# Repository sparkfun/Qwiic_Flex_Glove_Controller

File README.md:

SparkFun Qwiic Flex Glove Controller
========================================

[*SparkFun Qwiic Flex Glove Controller (Sen-14666)*](https://www.sparkfun.com/products/14666)

This board is a breakout for multiple flex sensors that keeps the solder points isolated to avoid breakage in wearable projects.

Repository Contents
-------------------

* **/Hardware** - Eagle design files (.brd, .sch)
* **/Libraries** - Libraries for use with the <PRODUCT NAME>
* **/Production** - Production panel files (.brd)

Documentation
--------------
* **[ADS1015 Library](https://github.com/sparkfun/SparkFun_ADS1015_Arduino_Library)** - C++ library for the ADS1015.
* **[Hookup Guide](https://learn.sparkfun.com/tutorials/qwiic-flex-glove-controller-hookup-guide)** - Basic hookup guide for the Qwiic Flex Glove Controller.

Product Versions
----------------
* [SEN-14666](https://www.sparkfun.com/products/14666)- The SparkFun Qwiic Flex Glove Controller allows you to incorporate flex sensors into a glove to control lighting, sound, and other effects making it perfect for wearable and e-textile applications. All communication is enacted exclusively via I2C, utilizing our handy Qwiic system. 

License Information
-------------------

This product is _**open source**_! 

Please review the LICENSE.md file for license information. 

If you have any questions or concerns on licensing, please contact techsupport@sparkfun.com.

Distributed as-is; no warranty is given.

- Your friends at SparkFun.

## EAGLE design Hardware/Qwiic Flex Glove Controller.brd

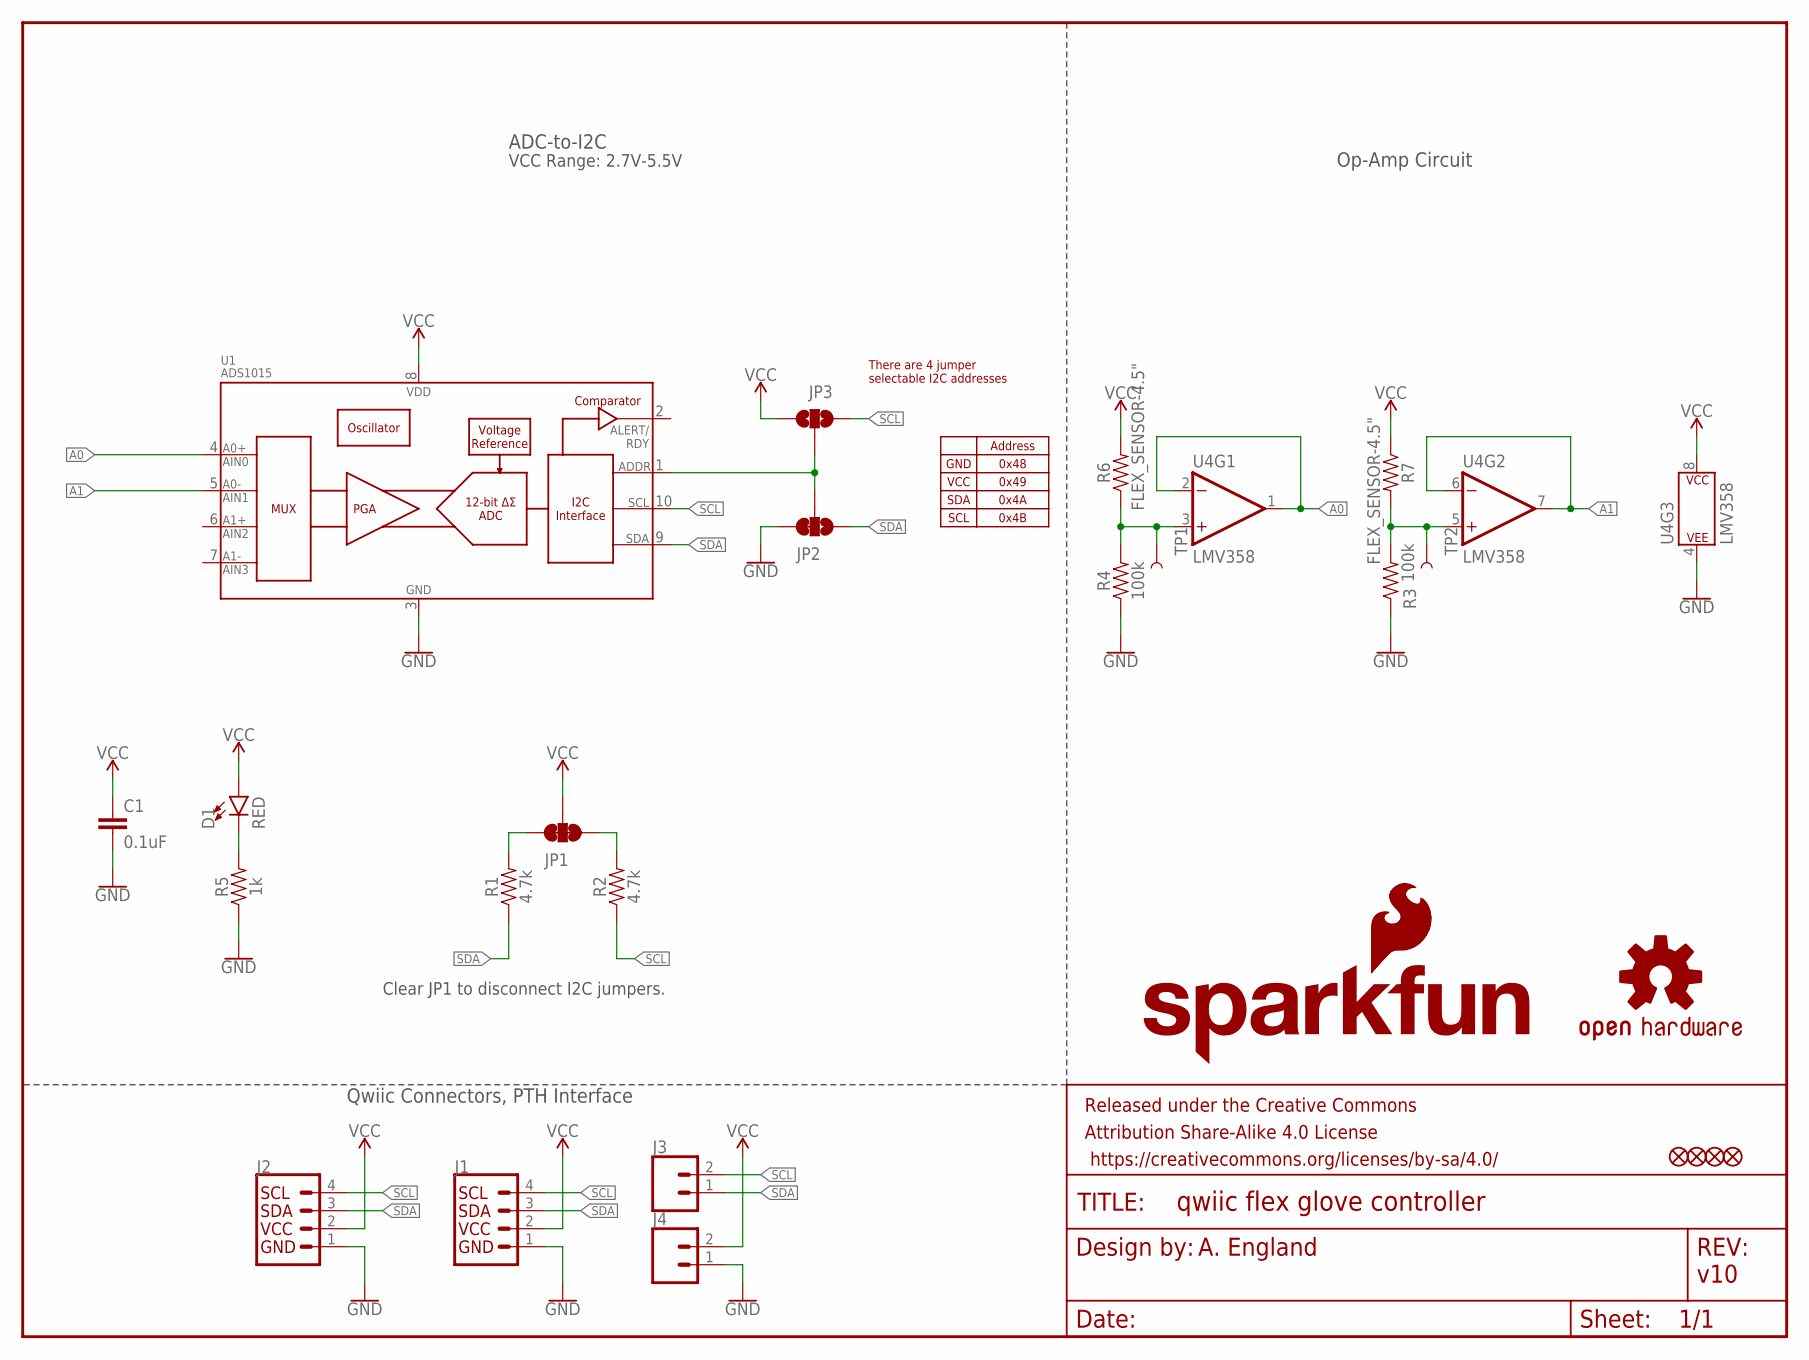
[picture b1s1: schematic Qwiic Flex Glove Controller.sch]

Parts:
C1: 0.1uF; 0603
D1: RED; LED-0603
FD1, FD2, FD3, FD4: FIDUCIALUFIDUCIAL; FIDUCIAL-MICRO
FRAME1: FRAME-LETTER; CREATIVE_COMMONS
J1, J2: QWIIC_CONNECTORJS-1MM; 1X04_1MM_RA
J3, J4: CONN_02; 1X02
JP1: JUMPER-SMT_3_2-NC_TRACE_NO-SILK; SMT-JUMPER_3_2-NC_TRACE_NO-SILK
JP2: JUMPER-SMT_3_1-NC_TRACE_NO-SILK; SMT-JUMPER_3_1-NC_TRACE_NO-SILK
JP3: JUMPER-SMT_3_NO_NO_SILK; SMT-JUMPER_3_0-NO_TRACE_NO-SILK
LOGO1: SFE_LOGO_NAME_FLAME.1_INCH; SFE_LOGO_NAME_FLAME_.1
LOGO2: OSHW-LOGOS; OSHW-LOGO-S
LOGO3: SFE_LOGO_FLAME.1_INCH; SFE_LOGO_FLAME_.1
R1, R2: 4.7k; 0603
R3, R4: 100k; 0603
R5: 1k; 0603
R6, R7: FLEX_SENSOR-4.5"; FLEX_SENSOR
TP1, TP2: TEST-POINT3; PAD.03X.03
U1: ADS1015; MSOP10
U4: LMV358; SO08

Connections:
A0: U1.4 (AIN0), U4.1 (OUT), U4.2 (-IN)
A1: U1.5 (AIN1), U4.6 (-IN), U4.7 (OUT)
GND: C1.2, J1.1, J2.1, J4.1, JP2.3, R3.1, R4.1, R5.1, U1.3 (VSS), U4.4 (P$V-)
unnamed: JP2.2, JP3.2, U1.1 (ADDR)
unnamed: D1.C, R5.2
unnamed: R3.2, R7.P$2 (2), TP2.P$1, U4.5 (+IN)
unnamed: R4.2, R6.P$1 (1), TP1.P$1, U4.3 (+IN)
unnamed: JP1.1, R2.2
unnamed: JP1.3, R1.2
SCL: J1.4, J2.4, J3.2, JP3.3, R2.1, U1.10 (SCL)
SDA: J1.3, J2.3, J3.1, JP2.1, R1.1, U1.9 (SDA)
VCC: C1.1, D1.A, J1.2, J2.2, J4.2, JP1.2, JP3.1, R6.P$2 (2), R7.P$1 (1), U1.8 (VDD), U4.8 (P$V+)

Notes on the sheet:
v10
Qwiic Connectors, PTH Interface
ADC-to-I2C
Op-Amp Circuit
A. England
There are 4 jumper selectable I2C addresses
Address
0x48
0x49
0x4A
0x4B
GND
VCC
SDA
SCL
VCC Range: 2.7V-5.5V
Clear JP1 to disconnect I2C jumpers.

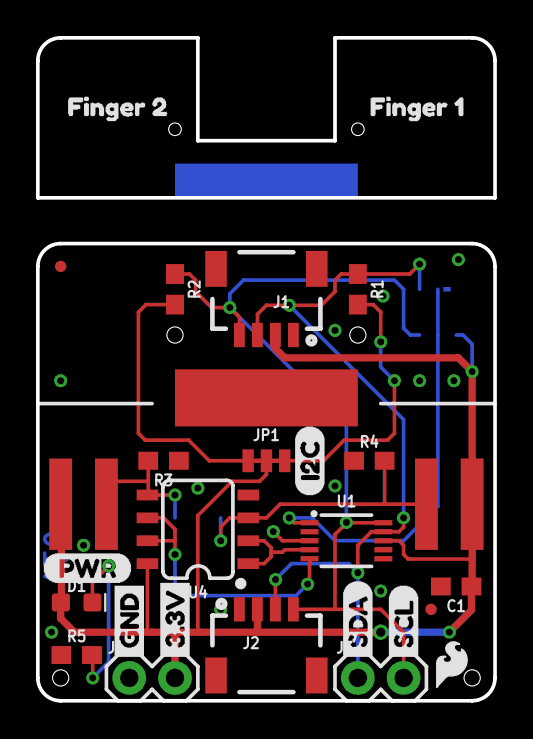
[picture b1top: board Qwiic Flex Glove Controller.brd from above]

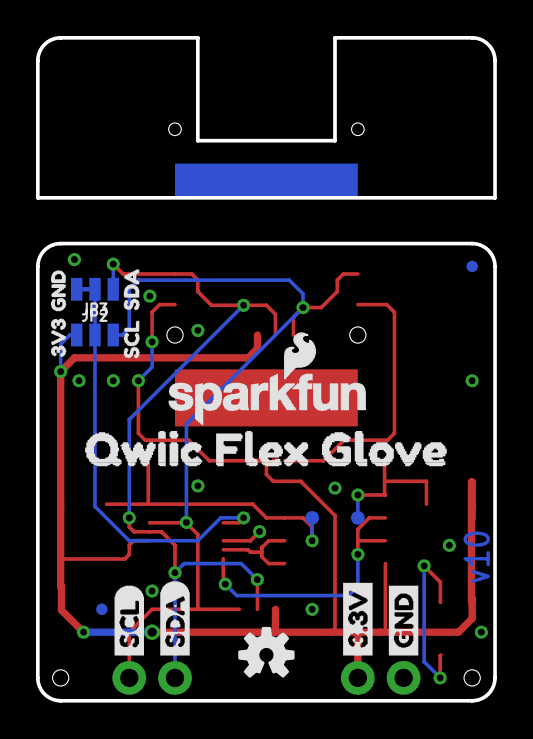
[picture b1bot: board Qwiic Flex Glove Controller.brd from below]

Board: 2 copper layers, 25.4 x 36.8 mm, 45 parts (17 on the bottom side), 12 nets.

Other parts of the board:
U$1, U$2: GND
U$3: 3V3-TEXT
U$4: GND-TEXT-03
U$5, U$6: 3.3V
U$7, U$8: SDA
U$9, U$10: SCL
U$11: (PWR)
U$12: SDA0
U$13: SCL2
U$14: QWIIC_FLEX_GLOVE0
U$15: I2C-()
U$16: FINGER_10
U$17: FINGER_21

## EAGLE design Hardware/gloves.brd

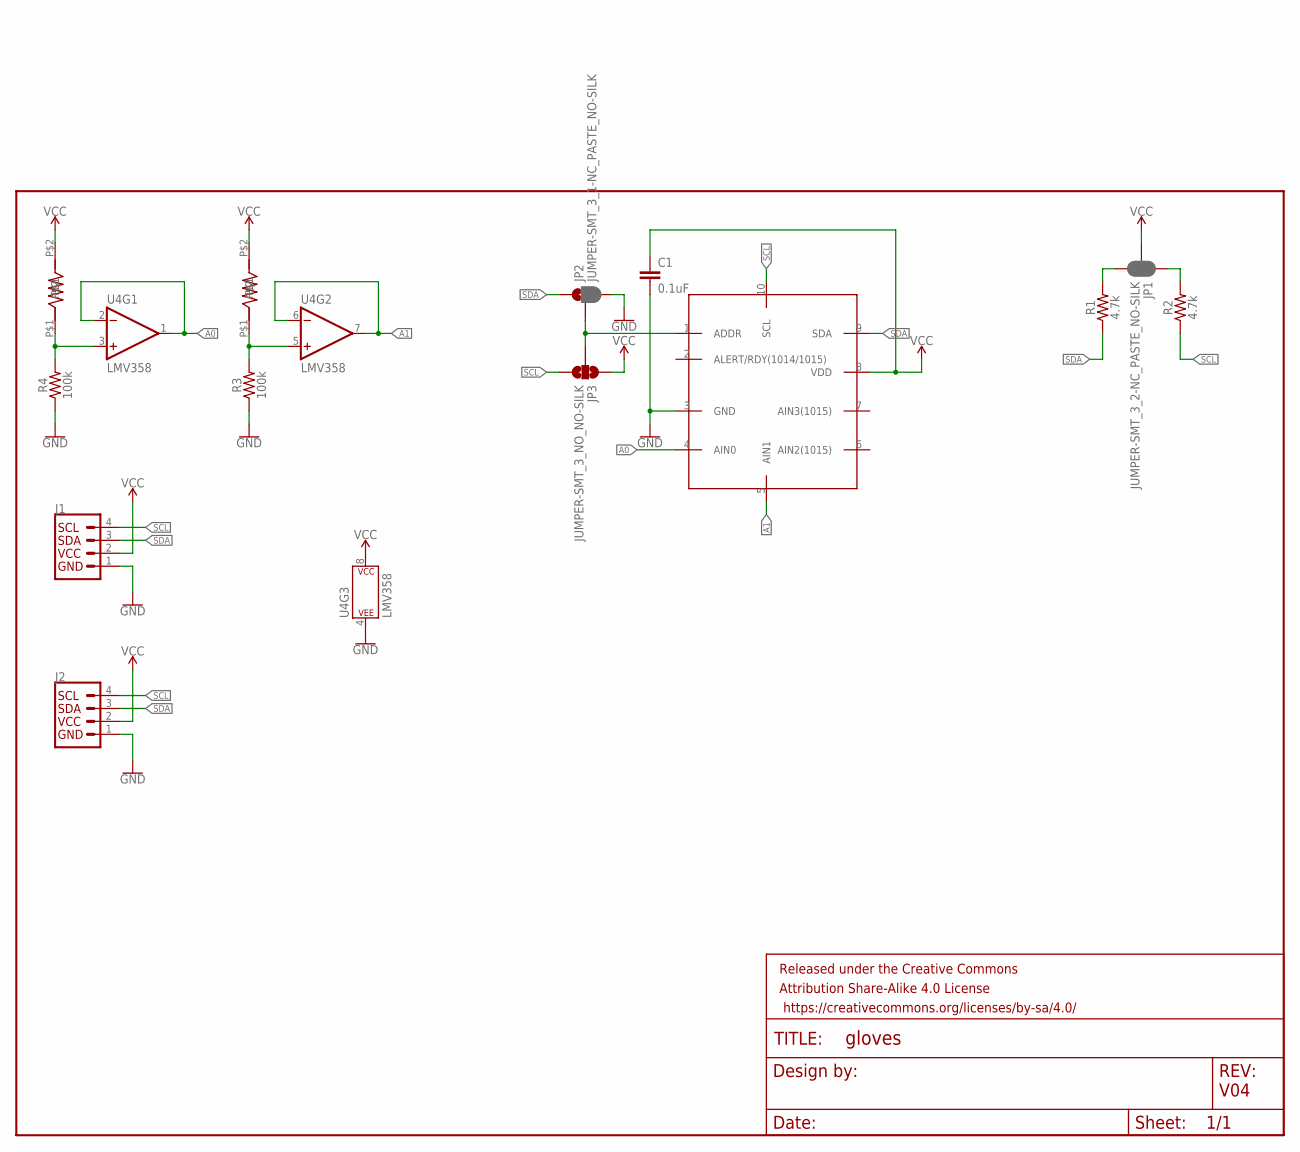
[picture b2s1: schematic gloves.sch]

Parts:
C1: 0.1uF; 0603
FRAME1: FRAME-LETTER; CREATIVE_COMMONS
J1, J2: QWIIC_CONNECTORJS-1MM; 1X04_1MM_RA
JP1: JUMPER-SMT_3_2-NC_PASTE_NO-SILK; SMT-JUMPER_3_2-NC_PASTE_NO-SILK
JP2: JUMPER-SMT_3_1-NC_PASTE_NO-SILK; SMT-JUMPER_3_1-NC_PASTE_NO-SILK
JP3: JUMPER-SMT_3_NO_NO-SILK; SMT-JUMPER_3_NO_NO-SILK
R1, R2: 4.7k; 0603
R3, R4: 100k; 0603
U4: LMV358; SO08
U$1: ADS101X-ADC_TO_I2CADS101X; MSOP-10-GNDPAD
U$3, U$4: FLEX_SENSOR

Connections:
A0: U4.1 (OUT), U4.2 (-IN), U$1.4 (AIN0)
A1: U4.6 (-IN), U4.7 (OUT), U$1.5 (AIN1)
GND: C1.2, J1.1, J2.1, JP2.3, R3.1, R4.1, U4.4 (P$V-), U$1.3 (GND)
unnamed: JP2.2, JP3.2, U$1.1 (ADDR)
unnamed: R3.2, U4.5 (+IN), U$3.P$1
unnamed: R4.2, U4.3 (+IN), U$4.P$1
unnamed: JP1.1, R2.2
unnamed: JP1.3, R1.2
SCL: J1.4, J2.4, JP3.3, R2.1, U$1.10 (SCL)
SDA: J1.3, J2.3, JP2.1, R1.1, U$1.9 (SDA)
VCC: C1.1, J1.2, J2.2, JP1.2, JP3.1, U4.8 (P$V+), U$1.8 (VDD), U$3.P$2, U$4.P$2

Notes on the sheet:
V04

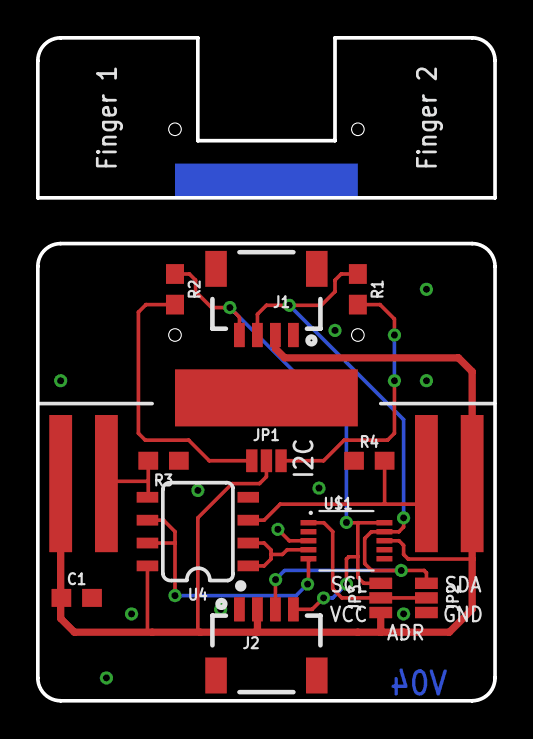
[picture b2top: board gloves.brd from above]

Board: 2 copper layers, 25.4 x 36.8 mm, 15 parts (0 on the bottom side), 11 nets.

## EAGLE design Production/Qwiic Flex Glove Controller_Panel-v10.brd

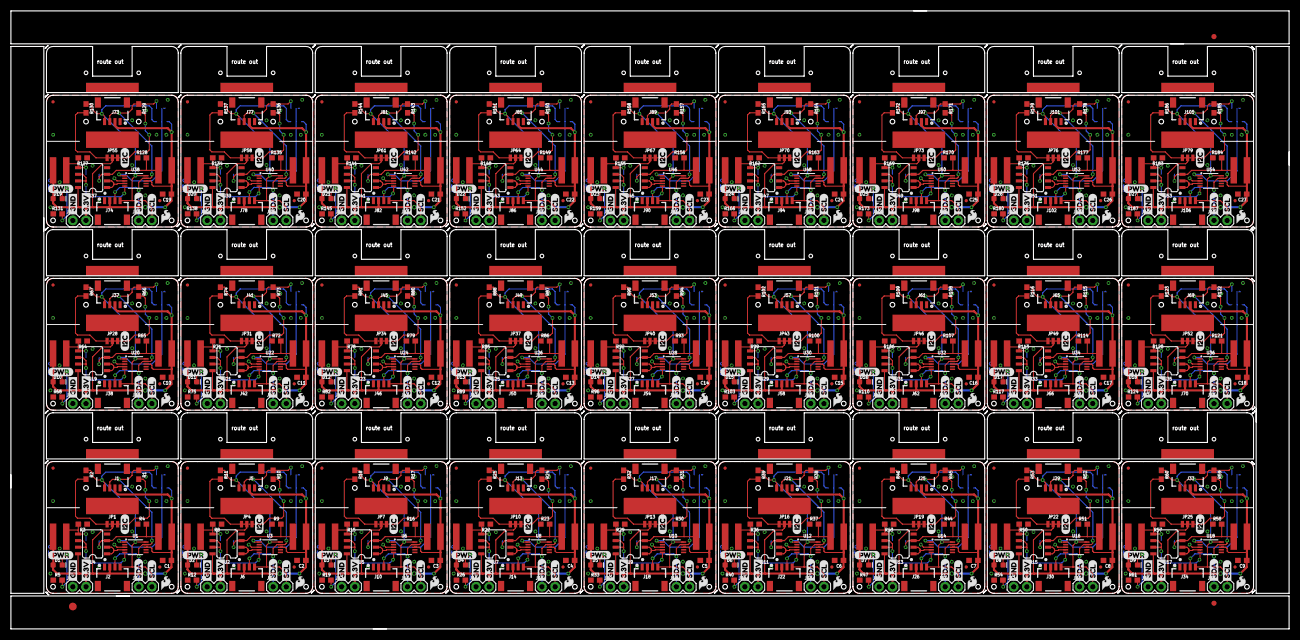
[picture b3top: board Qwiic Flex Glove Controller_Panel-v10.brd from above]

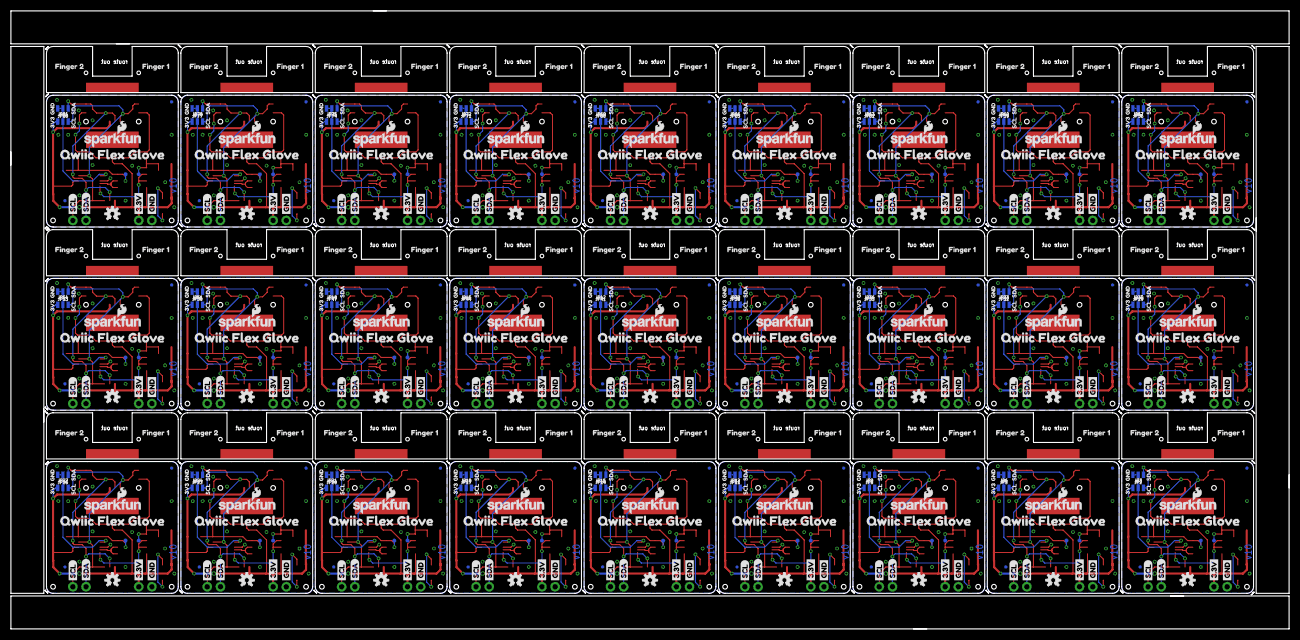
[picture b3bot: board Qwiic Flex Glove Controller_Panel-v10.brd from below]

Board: 2 copper layers, 246.4 x 119.1 mm, 1191 parts (513 on the bottom side), 324 nets.

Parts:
C1, C2, C3, C4, C5, C6, C7, C8, C9, C10, C11, C12, C13, C14, C15, C16, C17, C18, C19, C20, C21, C22, C23, C24, C25, C26, C27: 0.1uF; 0603
D1, D2, D3, D4, D5, D6, D7, D8, D9, D10, D11, D12, D13, D14, D15, D16, D17, D18, D19, D20, D21, D22, D23, D24, D25, D26, D27: RED; LED-0603
E$1: FIDUCIAL-1.5X3
E$5, E$6: FIDUCIAL-1X2
FD1, FD2, FD3, FD4, FD5, FD6, FD7, FD8, FD9, FD10, FD11, FD12, FD13, FD14, FD15, FD16, FD17, FD18, FD19, FD20, FD21, FD22, FD23, FD24, FD25, FD26, FD27, FD28, FD29, FD30, FD31, FD32, FD33, FD34, FD35, FD36, FD37, FD38, FD39, FD40, FD41, FD42, FD43, FD44, FD45, FD46, FD47, FD48, FD49, FD50, FD51, FD52, FD53, FD54, FD55, FD56, FD57, FD58, FD59, FD60, FD61, FD62, FD63, FD64, FD65, FD66, FD67, FD68, FD69, FD70, FD71, FD72, FD73, FD74, FD75, FD76, FD77, FD78, FD79, FD80, FD81, FD82, FD83, FD84, FD85, FD86, FD87, FD88, FD89, FD90, FD91, FD92, FD93, FD94, FD95, FD96, FD97, FD98, FD99, FD100, FD101, FD102, FD103, FD104, FD105, FD106, FD107, FD108: FIDUCIALUFIDUCIAL; FIDUCIAL-MICRO
J1, J2, J5, J6, J9, J10, J13, J14, J17, J18, J21, J22, J25, J26, J29, J30, J33, J34, J37, J38, J41, J42, J45, J46, J49, J50, J53, J54, J57, J58, J61, J62, J65, J66, J69, J70, J73, J74, J77, J78, J81, J82, J85, J86, J89, J90, J93, J94, J97, J98, J101, J102, J105, J106: 1X04_1MM_RA
J3, J4, J7, J8, J11, J12, J15, J16, J19, J20, J23, J24, J27, J28, J31, J32, J35, J36, J39, J40, J43, J44, J47, J48, J51, J52, J55, J56, J59, J60, J63, J64, J67, J68, J71, J72, J75, J76, J79, J80, J83, J84, J87, J88, J91, J92, J95, J96, J99, J100, J103, J104, J107, J108: 1X02
JP1, JP4, JP7, JP10, JP13, JP16, JP19, JP22, JP25, JP28, JP31, JP34, JP37, JP40, JP43, JP46, JP49, JP52, JP55, JP58, JP61, JP64, JP67, JP70, JP73, JP76, JP79: JUMPER-SMT_3_2-NC_TRACE_NO-SILK; SMT-JUMPER_3_2-NC_TRACE_NO-SILK
JP2, JP5, JP8, JP11, JP14, JP17, JP20, JP23, JP26, JP29, JP32, JP35, JP38, JP41, JP44, JP47, JP50, JP53, JP56, JP59, JP62, JP65, JP68, JP71, JP74, JP77, JP80: JUMPER-SMT_3_1-NC_TRACE_NO-SILK; SMT-JUMPER_3_1-NC_TRACE_NO-SILK
JP3, JP6, JP9, JP12, JP15, JP18, JP21, JP24, JP27, JP30, JP33, JP36, JP39, JP42, JP45, JP48, JP51, JP54, JP57, JP60, JP63, JP66, JP69, JP72, JP75, JP78, JP81: JUMPER-SMT_3_NO_NO_SILK; SMT-JUMPER_3_0-NO_TRACE_NO-SILK
LOGO1, LOGO4, LOGO7, LOGO10, LOGO13, LOGO16, LOGO19, LOGO22, LOGO25, LOGO28, LOGO31, LOGO34, LOGO37, LOGO40, LOGO43, LOGO46, LOGO49, LOGO52, LOGO55, LOGO58, LOGO61, LOGO64, LOGO67, LOGO70, LOGO73, LOGO76, LOGO79: SFE_LOGO_NAME_FLAME.1_INCH; SFE_LOGO_NAME_FLAME_.1
LOGO2, LOGO5, LOGO8, LOGO11, LOGO14, LOGO17, LOGO20, LOGO23, LOGO26, LOGO29, LOGO32, LOGO35, LOGO38, LOGO41, LOGO44, LOGO47, LOGO50, LOGO53, LOGO56, LOGO59, LOGO62, LOGO65, LOGO68, LOGO71, LOGO74, LOGO77, LOGO80: OSHW-LOGOS; OSHW-LOGO-S
LOGO3, LOGO6, LOGO9, LOGO12, LOGO15, LOGO18, LOGO21, LOGO24, LOGO27, LOGO30, LOGO33, LOGO36, LOGO39, LOGO42, LOGO45, LOGO48, LOGO51, LOGO54, LOGO57, LOGO60, LOGO63, LOGO66, LOGO69, LOGO72, LOGO75, LOGO78, LOGO81: SFE_LOGO_FLAME.1_INCH; SFE_LOGO_FLAME_.1
R1, R2, R10, R11, R17, R18, R24, R25, R31, R32, R38, R39, R45, R46, R52, R53, R59, R60, R66, R67, R73, R74, R80, R81, R87, R88, R94, R95, R101, R102, R108, R109, R115, R116, R122, R123, R129, R130, R136, R137, R143, R144, R150, R151, R157, R158, R164, R165, R171, R172, R178, R179, R185, R186: 4.7k; 0603
R3, R4, R8, R9, R15, R16, R22, R23, R29, R30, R36, R37, R43, R44, R50, R51, R57, R58, R64, R65, R71, R72, R78, R79, R85, R86, R92, R93, R99, R100, R106, R107, R113, R114, R120, R121, R127, R128, R134, R135, R141, R142, R148, R149, R155, R156, R162, R163, R169, R170, R176, R177, R183, R184: 100k; 0603
R5, R12, R19, R26, R33, R40, R47, R54, R61, R68, R75, R82, R89, R96, R103, R110, R117, R124, R131, R138, R145, R152, R159, R166, R173, R180, R187: 1k; 0603
R6, R7, R13, R14, R20, R21, R27, R28, R34, R35, R41, R42, R48, R49, R55, R56, R62, R63, R69, R70, R76, R77, R83, R84, R90, R91, R97, R98, R104, R105, R111, R112, R118, R119, R125, R126, R132, R133, R139, R140, R146, R147, R153, R154, R160, R161, R167, R168, R174, R175, R181, R182, R188, R189: FLEX_SENSOR-4.5"; FLEX_SENSOR
TP1, TP2, TP3, TP4, TP5, TP6, TP7, TP8, TP9, TP10, TP11, TP12, TP13, TP14, TP15, TP16, TP17, TP18, TP19, TP20, TP21, TP22, TP23, TP24, TP25, TP26, TP27, TP28, TP29, TP30, TP31, TP32, TP33, TP34, TP35, TP36, TP37, TP38, TP39, TP40, TP41, TP42, TP43, TP44, TP45, TP46, TP47, TP48, TP49, TP50, TP51, TP52, TP53, TP54: TEST-POINT3; PAD.03X.03
U1, U3, U6, U8, U10, U12, U14, U16, U18, U20, U22, U24, U26, U28, U30, U32, U34, U36, U38, U40, U42, U44, U46, U48, U50, U52, U54: ADS1015; MSOP10
U2, U4, U5, U7, U9, U11, U13, U15, U17, U19, U21, U23, U25, U27, U29, U31, U33, U35, U37, U39, U41, U43, U45, U47, U49, U51, U53: LMV358; SO08
U$1, U$2, U$18, U$19, U$35, U$36, U$52, U$53, U$69, U$70, U$86, U$87, U$103, U$104, U$120, U$121, U$137, U$138, U$154, U$155, U$171, U$172, U$188, U$189, U$205, U$206, U$222, U$223, U$239, U$240, U$256, U$257, U$273, U$274, U$290, U$291, U$307, U$308, U$324, U$325, U$341, U$342, U$358, U$359, U$375, U$376, U$392, U$393, U$409, U$410, U$426, U$427, U$443, U$444: GND
U$3, U$27, U$44, U$61, U$78, U$95, U$112, U$129, U$146, U$163, U$180, U$197, U$214, U$231, U$248, U$265, U$282, U$299, U$316, U$333, U$350, U$367, U$384, U$401, U$418, U$435, U$452: 3V3-TEXT
U$4, U$28, U$45, U$62, U$79, U$96, U$113, U$130, U$147, U$164, U$181, U$198, U$215, U$232, U$249, U$266, U$283, U$300, U$317, U$334, U$351, U$368, U$385, U$402, U$419, U$436, U$453: GND-TEXT-03
U$5, U$6, U$20, U$21, U$37, U$38, U$54, U$55, U$71, U$72, U$88, U$89, U$105, U$106, U$122, U$123, U$139, U$140, U$156, U$157, U$173, U$174, U$190, U$191, U$207, U$208, U$224, U$225, U$241, U$242, U$258, U$259, U$275, U$276, U$292, U$293, U$309, U$310, U$326, U$327, U$343, U$344, U$360, U$361, U$377, U$378, U$394, U$395, U$411, U$412, U$428, U$429, U$445, U$446: 3.3V
U$7, U$8, U$22, U$23, U$39, U$40, U$56, U$57, U$73, U$74, U$90, U$91, U$107, U$108, U$124, U$125, U$141, U$142, U$158, U$159, U$175, U$176, U$192, U$193, U$209, U$210, U$226, U$227, U$243, U$244, U$260, U$261, U$277, U$278, U$294, U$295, U$311, U$312, U$328, U$329, U$345, U$346, U$362, U$363, U$379, U$380, U$396, U$397, U$413, U$414, U$430, U$431, U$447, U$448: SDA
U$9, U$10, U$24, U$25, U$41, U$42, U$58, U$59, U$75, U$76, U$92, U$93, U$109, U$110, U$126, U$127, U$143, U$144, U$160, U$161, U$177, U$178, U$194, U$195, U$211, U$212, U$228, U$229, U$245, U$246, U$262, U$263, U$279, U$280, U$296, U$297, U$313, U$314, U$330, U$331, U$347, U$348, U$364, U$365, U$381, U$382, U$398, U$399, U$415, U$416, U$432, U$433, U$449, U$450: SCL
U$11, U$26, U$43, U$60, U$77, U$94, U$111, U$128, U$145, U$162, U$179, U$196, U$213, U$230, U$247, U$264, U$281, U$298, U$315, U$332, U$349, U$366, U$383, U$400, U$417, U$434, U$451: (PWR)
U$12, U$29, U$46, U$63, U$80, U$97, U$114, U$131, U$148, U$165, U$182, U$199, U$216, U$233, U$250, U$267, U$284, U$301, U$318, U$335, U$352, U$369, U$386, U$403, U$420, U$437, U$454: SDA0
U$13, U$30, U$47, U$64, U$81, U$98, U$115, U$132, U$149, U$166, U$183, U$200, U$217, U$234, U$251, U$268, U$285, U$302, U$319, U$336, U$353, U$370, U$387, U$404, U$421, U$438, U$455: SCL2
U$14, U$32, U$49, U$66, U$83, U$100, U$117, U$134, U$151, U$168, U$185, U$202, U$219, U$236, U$253, U$270, U$287, U$304, U$321, U$338, U$355, U$372, U$389, U$406, U$423, U$440, U$457: QWIIC_FLEX_GLOVE0
U$15, U$31, U$48, U$65, U$82, U$99, U$116, U$133, U$150, U$167, U$184, U$201, U$218, U$235, U$252, U$269, U$286, U$303, U$320, U$337, U$354, U$371, U$388, U$405, U$422, U$439, U$456: I2C-()
U$16, U$33, U$50, U$67, U$84, U$101, U$118, U$135, U$152, U$169, U$186, U$203, U$220, U$237, U$254, U$271, U$288, U$305, U$322, U$339, U$356, U$373, U$390, U$407, U$424, U$441, U$458: FINGER_10
U$17, U$34, U$51, U$68, U$85, U$102, U$119, U$136, U$153, U$170, U$187, U$204, U$221, U$238, U$255, U$272, U$289, U$306, U$323, U$340, U$357, U$374, U$391, U$408, U$425, U$442, U$459: FINGER_21

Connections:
A0: U1.4, U4.1, U4.2
A1: U1.5, U4.6, U4.7
A2: U2.1, U2.2, U3.4
A3: U2.6, U2.7, U3.5
A4: U5.1, U5.2, U6.4
A5: U5.6, U5.7, U6.5
A6: U7.1, U7.2, U8.4
A7: U7.6, U7.7, U8.5
A8: U9.1, U9.2, U10.4
A9: U9.6, U9.7, U10.5
A10: U11.1, U11.2, U12.4
A11: U11.6, U11.7, U12.5
A12: U13.1, U13.2, U14.4
A13: U13.6, U13.7, U14.5
A14: U15.1, U15.2, U16.4
A15: U15.6, U15.7, U16.5
A16: U17.1, U17.2, U18.4
A17: U17.6, U17.7, U18.5
A18: U19.1, U19.2, U20.4
A19: U19.6, U19.7, U20.5
A20: U21.1, U21.2, U22.4
A21: U21.6, U21.7, U22.5
A22: U23.1, U23.2, U24.4
A23: U23.6, U23.7, U24.5
A24: U25.1, U25.2, U26.4
A25: U25.6, U25.7, U26.5
A26: U27.1, U27.2, U28.4
A27: U27.6, U27.7, U28.5
A28: U29.1, U29.2, U30.4
A29: U29.6, U29.7, U30.5
A30: U31.1, U31.2, U32.4
A31: U31.6, U31.7, U32.5
A32: U33.1, U33.2, U34.4
A33: U33.6, U33.7, U34.5
A34: U35.1, U35.2, U36.4
A35: U35.6, U35.7, U36.5
A36: U37.1, U37.2, U38.4
A37: U37.6, U37.7, U38.5
A38: U39.1, U39.2, U40.4
A39: U39.6, U39.7, U40.5
A40: U41.1, U41.2, U42.4
A41: U41.6, U41.7, U42.5
A42: U43.1, U43.2, U44.4
A43: U43.6, U43.7, U44.5
A44: U45.1, U45.2, U46.4
A45: U45.6, U45.7, U46.5
A46: U47.1, U47.2, U48.4
A47: U47.6, U47.7, U48.5
A48: U49.1, U49.2, U50.4
A49: U49.6, U49.7, U50.5
A50: U51.1, U51.2, U52.4
A51: U51.6, U51.7, U52.5
A52: U53.1, U53.2, U54.4
A53: U53.6, U53.7, U54.5
GND: C1.2, J1.1, J2.1, J4.1, JP2.3, R3.1, R4.1, R5.1, U1.3, U4.4
GND1: C2.2, J5.1, J6.1, J8.1, JP5.3, R8.1, R9.1, R12.1, U2.4, U3.3
GND2: C3.2, J9.1, J10.1, J12.1, JP8.3, R15.1, R16.1, R19.1, U5.4, U6.3
GND3: C4.2, J13.1, J14.1, J16.1, JP11.3, R22.1, R23.1, R26.1, U7.4, U8.3
GND4: C5.2, J17.1, J18.1, J20.1, JP14.3, R29.1, R30.1, R33.1, U9.4, U10.3
GND5: C6.2, J21.1, J22.1, J24.1, JP17.3, R36.1, R37.1, R40.1, U11.4, U12.3
GND6: C7.2, J25.1, J26.1, J28.1, JP20.3, R43.1, R44.1, R47.1, U13.4, U14.3
GND7: C8.2, J29.1, J30.1, J32.1, JP23.3, R50.1, R51.1, R54.1, U15.4, U16.3
GND8: C9.2, J33.1, J34.1, J36.1, JP26.3, R57.1, R58.1, R61.1, U17.4, U18.3
GND9: C10.2, J37.1, J38.1, J40.1, JP29.3, R64.1, R65.1, R68.1, U19.4, U20.3
GND10: C11.2, J41.1, J42.1, J44.1, JP32.3, R71.1, R72.1, R75.1, U21.4, U22.3
GND11: C12.2, J45.1, J46.1, J48.1, JP35.3, R78.1, R79.1, R82.1, U23.4, U24.3
GND12: C13.2, J49.1, J50.1, J52.1, JP38.3, R85.1, R86.1, R89.1, U25.4, U26.3
GND13: C14.2, J53.1, J54.1, J56.1, JP41.3, R92.1, R93.1, R96.1, U27.4, U28.3
GND14: C15.2, J57.1, J58.1, J60.1, JP44.3, R99.1, R100.1, R103.1, U29.4, U30.3
GND15: C16.2, J61.1, J62.1, J64.1, JP47.3, R106.1, R107.1, R110.1, U31.4, U32.3
GND16: C17.2, J65.1, J66.1, J68.1, JP50.3, R113.1, R114.1, R117.1, U33.4, U34.3
GND17: C18.2, J69.1, J70.1, J72.1, JP53.3, R120.1, R121.1, R124.1, U35.4, U36.3
GND18: C19.2, J73.1, J74.1, J76.1, JP56.3, R127.1, R128.1, R131.1, U37.4, U38.3
GND19: C20.2, J77.1, J78.1, J80.1, JP59.3, R134.1, R135.1, R138.1, U39.4, U40.3
GND20: C21.2, J81.1, J82.1, J84.1, JP62.3, R141.1, R142.1, R145.1, U41.4, U42.3
GND21: C22.2, J85.1, J86.1, J88.1, JP65.3, R148.1, R149.1, R152.1, U43.4, U44.3
GND22: C23.2, J89.1, J90.1, J92.1, JP68.3, R155.1, R156.1, R159.1, U45.4, U46.3
GND23: C24.2, J93.1, J94.1, J96.1, JP71.3, R162.1, R163.1, R166.1, U47.4, U48.3
GND24: C25.2, J97.1, J98.1, J100.1, JP74.3, R169.1, R170.1, R173.1, U49.4, U50.3
GND25: C26.2, J101.1, J102.1, J104.1, JP77.3, R176.1, R177.1, R180.1, U51.4, U52.3
GND26: C27.2, J105.1, J106.1, J108.1, JP80.3, R183.1, R184.1, R187.1, U53.4, U54.3
unnamed: JP2.2, JP3.2, U1.1
unnamed: D1.C, R5.2
unnamed: R3.2, R7.P$2, TP2.P$1, U4.5
unnamed: R4.2, R6.P$1, TP1.P$1, U4.3
unnamed: R8.2, R14.P$2, TP4.P$1, U2.5
unnamed: R9.2, R13.P$1, TP3.P$1, U2.3
unnamed: JP1.1, R2.2
unnamed: JP1.3, R1.2
unnamed: JP4.1, R11.2
unnamed: JP4.3, R10.2
unnamed: JP5.2, JP6.2, U3.1
unnamed: D2.C, R12.2
unnamed: R15.2, R21.P$2, TP6.P$1, U5.5
unnamed: R16.2, R20.P$1, TP5.P$1, U5.3
unnamed: JP7.1, R18.2
unnamed: JP7.3, R17.2
unnamed: JP8.2, JP9.2, U6.1
unnamed: D3.C, R19.2
unnamed: R22.2, R28.P$2, TP8.P$1, U7.5
unnamed: R23.2, R27.P$1, TP7.P$1, U7.3
unnamed: JP10.1, R25.2
unnamed: JP10.3, R24.2
unnamed: JP11.2, JP12.2, U8.1
unnamed: D4.C, R26.2
unnamed: R29.2, R35.P$2, TP10.P$1, U9.5
unnamed: R30.2, R34.P$1, TP9.P$1, U9.3
unnamed: JP13.1, R32.2
unnamed: JP13.3, R31.2
unnamed: JP14.2, JP15.2, U10.1
unnamed: D5.C, R33.2
unnamed: R36.2, R42.P$2, TP12.P$1, U11.5
unnamed: R37.2, R41.P$1, TP11.P$1, U11.3
unnamed: JP16.1, R39.2
unnamed: JP16.3, R38.2
unnamed: JP17.2, JP18.2, U12.1
unnamed: D6.C, R40.2
unnamed: R43.2, R49.P$2, TP14.P$1, U13.5
unnamed: R44.2, R48.P$1, TP13.P$1, U13.3
unnamed: JP19.1, R46.2
unnamed: JP19.3, R45.2
unnamed: JP20.2, JP21.2, U14.1
unnamed: D7.C, R47.2
unnamed: R50.2, R56.P$2, TP16.P$1, U15.5
unnamed: R51.2, R55.P$1, TP15.P$1, U15.3
unnamed: JP22.1, R53.2
unnamed: JP22.3, R52.2
unnamed: JP23.2, JP24.2, U16.1
unnamed: D8.C, R54.2
unnamed: R57.2, R63.P$2, TP18.P$1, U17.5
unnamed: R58.2, R62.P$1, TP17.P$1, U17.3
unnamed: JP25.1, R60.2
unnamed: JP25.3, R59.2
unnamed: JP26.2, JP27.2, U18.1
unnamed: D9.C, R61.2
unnamed: R64.2, R70.P$2, TP20.P$1, U19.5
unnamed: R65.2, R69.P$1, TP19.P$1, U19.3
unnamed: JP28.1, R67.2
unnamed: JP28.3, R66.2
unnamed: JP29.2, JP30.2, U20.1
unnamed: D10.C, R68.2
unnamed: R71.2, R77.P$2, TP22.P$1, U21.5
unnamed: R72.2, R76.P$1, TP21.P$1, U21.3
unnamed: JP31.1, R74.2
unnamed: JP31.3, R73.2
unnamed: JP32.2, JP33.2, U22.1
unnamed: D11.C, R75.2
unnamed: R78.2, R84.P$2, TP24.P$1, U23.5
unnamed: R79.2, R83.P$1, TP23.P$1, U23.3
unnamed: JP34.1, R81.2
unnamed: JP34.3, R80.2
unnamed: JP35.2, JP36.2, U24.1
unnamed: D12.C, R82.2
unnamed: R85.2, R91.P$2, TP26.P$1, U25.5
unnamed: R86.2, R90.P$1, TP25.P$1, U25.3
unnamed: JP37.1, R88.2
unnamed: JP37.3, R87.2
unnamed: JP38.2, JP39.2, U26.1
unnamed: D13.C, R89.2
unnamed: R92.2, R98.P$2, TP28.P$1, U27.5
unnamed: R93.2, R97.P$1, TP27.P$1, U27.3
unnamed: JP40.1, R95.2
unnamed: JP40.3, R94.2
unnamed: JP41.2, JP42.2, U28.1
unnamed: D14.C, R96.2
unnamed: R99.2, R105.P$2, TP30.P$1, U29.5
unnamed: R100.2, R104.P$1, TP29.P$1, U29.3
unnamed: JP43.1, R102.2
unnamed: JP43.3, R101.2
unnamed: JP44.2, JP45.2, U30.1
unnamed: D15.C, R103.2
unnamed: R106.2, R112.P$2, TP32.P$1, U31.5
unnamed: R107.2, R111.P$1, TP31.P$1, U31.3
unnamed: JP46.1, R109.2
unnamed: JP46.3, R108.2
unnamed: JP47.2, JP48.2, U32.1
unnamed: D16.C, R110.2
unnamed: R113.2, R119.P$2, TP34.P$1, U33.5
unnamed: R114.2, R118.P$1, TP33.P$1, U33.3
unnamed: JP49.1, R116.2
unnamed: JP49.3, R115.2
unnamed: JP50.2, JP51.2, U34.1
unnamed: D17.C, R117.2
unnamed: R120.2, R126.P$2, TP36.P$1, U35.5
unnamed: R121.2, R125.P$1, TP35.P$1, U35.3
unnamed: JP52.1, R123.2
unnamed: JP52.3, R122.2
unnamed: JP53.2, JP54.2, U36.1
unnamed: D18.C, R124.2
unnamed: R127.2, R133.P$2, TP38.P$1, U37.5
unnamed: R128.2, R132.P$1, TP37.P$1, U37.3
unnamed: JP55.1, R130.2
unnamed: JP55.3, R129.2
unnamed: JP56.2, JP57.2, U38.1
unnamed: D19.C, R131.2
unnamed: R134.2, R140.P$2, TP40.P$1, U39.5
unnamed: R135.2, R139.P$1, TP39.P$1, U39.3
unnamed: JP58.1, R137.2
unnamed: JP58.3, R136.2
unnamed: JP59.2, JP60.2, U40.1
unnamed: D20.C, R138.2
unnamed: R141.2, R147.P$2, TP42.P$1, U41.5
unnamed: R142.2, R146.P$1, TP41.P$1, U41.3
unnamed: JP61.1, R144.2
unnamed: JP61.3, R143.2
unnamed: JP62.2, JP63.2, U42.1
unnamed: D21.C, R145.2
unnamed: R148.2, R154.P$2, TP44.P$1, U43.5
unnamed: R149.2, R153.P$1, TP43.P$1, U43.3
unnamed: JP64.1, R151.2
unnamed: JP64.3, R150.2
unnamed: JP65.2, JP66.2, U44.1
unnamed: D22.C, R152.2
unnamed: R155.2, R161.P$2, TP46.P$1, U45.5
unnamed: R156.2, R160.P$1, TP45.P$1, U45.3
unnamed: JP67.1, R158.2
unnamed: JP67.3, R157.2
unnamed: JP68.2, JP69.2, U46.1
unnamed: D23.C, R159.2
unnamed: R162.2, R168.P$2, TP48.P$1, U47.5
unnamed: R163.2, R167.P$1, TP47.P$1, U47.3
unnamed: JP70.1, R165.2
unnamed: JP70.3, R164.2
unnamed: JP71.2, JP72.2, U48.1
unnamed: D24.C, R166.2
unnamed: R169.2, R175.P$2, TP50.P$1, U49.5
unnamed: R170.2, R174.P$1, TP49.P$1, U49.3
unnamed: JP73.1, R172.2
unnamed: JP73.3, R171.2
unnamed: JP74.2, JP75.2, U50.1
unnamed: D25.C, R173.2
unnamed: R176.2, R182.P$2, TP52.P$1, U51.5
unnamed: R177.2, R181.P$1, TP51.P$1, U51.3
unnamed: JP76.1, R179.2
unnamed: JP76.3, R178.2
unnamed: JP77.2, JP78.2, U52.1
unnamed: D26.C, R180.2
unnamed: R183.2, R189.P$2, TP54.P$1, U53.5
unnamed: R184.2, R188.P$1, TP53.P$1, U53.3
unnamed: JP79.1, R186.2
unnamed: JP79.3, R185.2
unnamed: JP80.2, JP81.2, U54.1
unnamed: D27.C, R187.2
SCL: J1.4, J2.4, J3.2, JP3.3, R2.1, U1.10
SCL1: J5.4, J6.4, J7.2, JP6.3, R11.1, U3.10
SCL2: J9.4, J10.4, J11.2, JP9.3, R18.1, U6.10
SCL3: J13.4, J14.4, J15.2, JP12.3, R25.1, U8.10
SCL4: J17.4, J18.4, J19.2, JP15.3, R32.1, U10.10
SCL5: J21.4, J22.4, J23.2, JP18.3, R39.1, U12.10
SCL6: J25.4, J26.4, J27.2, JP21.3, R46.1, U14.10
SCL7: J29.4, J30.4, J31.2, JP24.3, R53.1, U16.10
SCL8: J33.4, J34.4, J35.2, JP27.3, R60.1, U18.10
SCL9: J37.4, J38.4, J39.2, JP30.3, R67.1, U20.10
SCL10: J41.4, J42.4, J43.2, JP33.3, R74.1, U22.10
SCL11: J45.4, J46.4, J47.2, JP36.3, R81.1, U24.10
SCL12: J49.4, J50.4, J51.2, JP39.3, R88.1, U26.10
SCL13: J53.4, J54.4, J55.2, JP42.3, R95.1, U28.10
SCL14: J57.4, J58.4, J59.2, JP45.3, R102.1, U30.10
SCL15: J61.4, J62.4, J63.2, JP48.3, R109.1, U32.10
SCL16: J65.4, J66.4, J67.2, JP51.3, R116.1, U34.10
SCL17: J69.4, J70.4, J71.2, JP54.3, R123.1, U36.10
SCL18: J73.4, J74.4, J75.2, JP57.3, R130.1, U38.10
SCL19: J77.4, J78.4, J79.2, JP60.3, R137.1, U40.10
SCL20: J81.4, J82.4, J83.2, JP63.3, R144.1, U42.10
SCL21: J85.4, J86.4, J87.2, JP66.3, R151.1, U44.10
SCL22: J89.4, J90.4, J91.2, JP69.3, R158.1, U46.10
SCL23: J93.4, J94.4, J95.2, JP72.3, R165.1, U48.10
SCL24: J97.4, J98.4, J99.2, JP75.3, R172.1, U50.10
SCL25: J101.4, J102.4, J103.2, JP78.3, R179.1, U52.10
SCL26: J105.4, J106.4, J107.2, JP81.3, R186.1, U54.10
SDA: J1.3, J2.3, J3.1, JP2.1, R1.1, U1.9
SDA1: J5.3, J6.3, J7.1, JP5.1, R10.1, U3.9
SDA2: J9.3, J10.3, J11.1, JP8.1, R17.1, U6.9
SDA3: J13.3, J14.3, J15.1, JP11.1, R24.1, U8.9
SDA4: J17.3, J18.3, J19.1, JP14.1, R31.1, U10.9
SDA5: J21.3, J22.3, J23.1, JP17.1, R38.1, U12.9
SDA6: J25.3, J26.3, J27.1, JP20.1, R45.1, U14.9
SDA7: J29.3, J30.3, J31.1, JP23.1, R52.1, U16.9
SDA8: J33.3, J34.3, J35.1, JP26.1, R59.1, U18.9
SDA9: J37.3, J38.3, J39.1, JP29.1, R66.1, U20.9
SDA10: J41.3, J42.3, J43.1, JP32.1, R73.1, U22.9
SDA11: J45.3, J46.3, J47.1, JP35.1, R80.1, U24.9
SDA12: J49.3, J50.3, J51.1, JP38.1, R87.1, U26.9
SDA13: J53.3, J54.3, J55.1, JP41.1, R94.1, U28.9
SDA14: J57.3, J58.3, J59.1, JP44.1, R101.1, U30.9
SDA15: J61.3, J62.3, J63.1, JP47.1, R108.1, U32.9
SDA16: J65.3, J66.3, J67.1, JP50.1, R115.1, U34.9
SDA17: J69.3, J70.3, J71.1, JP53.1, R122.1, U36.9
SDA18: J73.3, J74.3, J75.1, JP56.1, R129.1, U38.9
SDA19: J77.3, J78.3, J79.1, JP59.1, R136.1, U40.9
SDA20: J81.3, J82.3, J83.1, JP62.1, R143.1, U42.9
SDA21: J85.3, J86.3, J87.1, JP65.1, R150.1, U44.9
SDA22: J89.3, J90.3, J91.1, JP68.1, R157.1, U46.9
SDA23: J93.3, J94.3, J95.1, JP71.1, R164.1, U48.9
SDA24: J97.3, J98.3, J99.1, JP74.1, R171.1, U50.9
SDA25: J101.3, J102.3, J103.1, JP77.1, R178.1, U52.9
SDA26: J105.3, J106.3, J107.1, JP80.1, R185.1, U54.9
VCC: C1.1, D1.A, J1.2, J2.2, J4.2, JP1.2, JP3.1, R6.P$2, R7.P$1, U1.8, U4.8
VCC1: C2.1, D2.A, J5.2, J6.2, J8.2, JP4.2, JP6.1, R13.P$2, R14.P$1, U2.8, U3.8
VCC2: C3.1, D3.A, J9.2, J10.2, J12.2, JP7.2, JP9.1, R20.P$2, R21.P$1, U5.8, U6.8
VCC3: C4.1, D4.A, J13.2, J14.2, J16.2, JP10.2, JP12.1, R27.P$2, R28.P$1, U7.8, U8.8
VCC4: C5.1, D5.A, J17.2, J18.2, J20.2, JP13.2, JP15.1, R34.P$2, R35.P$1, U9.8, U10.8
VCC5: C6.1, D6.A, J21.2, J22.2, J24.2, JP16.2, JP18.1, R41.P$2, R42.P$1, U11.8, U12.8
VCC6: C7.1, D7.A, J25.2, J26.2, J28.2, JP19.2, JP21.1, R48.P$2, R49.P$1, U13.8, U14.8
VCC7: C8.1, D8.A, J29.2, J30.2, J32.2, JP22.2, JP24.1, R55.P$2, R56.P$1, U15.8, U16.8
VCC8: C9.1, D9.A, J33.2, J34.2, J36.2, JP25.2, JP27.1, R62.P$2, R63.P$1, U17.8, U18.8
VCC9: C10.1, D10.A, J37.2, J38.2, J40.2, JP28.2, JP30.1, R69.P$2, R70.P$1, U19.8, U20.8
VCC10: C11.1, D11.A, J41.2, J42.2, J44.2, JP31.2, JP33.1, R76.P$2, R77.P$1, U21.8, U22.8
VCC11: C12.1, D12.A, J45.2, J46.2, J48.2, JP34.2, JP36.1, R83.P$2, R84.P$1, U23.8, U24.8
VCC12: C13.1, D13.A, J49.2, J50.2, J52.2, JP37.2, JP39.1, R90.P$2, R91.P$1, U25.8, U26.8
VCC13: C14.1, D14.A, J53.2, J54.2, J56.2, JP40.2, JP42.1, R97.P$2, R98.P$1, U27.8, U28.8
VCC14: C15.1, D15.A, J57.2, J58.2, J60.2, JP43.2, JP45.1, R104.P$2, R105.P$1, U29.8, U30.8
VCC15: C16.1, D16.A, J61.2, J62.2, J64.2, JP46.2, JP48.1, R111.P$2, R112.P$1, U31.8, U32.8
VCC16: C17.1, D17.A, J65.2, J66.2, J68.2, JP49.2, JP51.1, R118.P$2, R119.P$1, U33.8, U34.8
VCC17: C18.1, D18.A, J69.2, J70.2, J72.2, JP52.2, JP54.1, R125.P$2, R126.P$1, U35.8, U36.8
VCC18: C19.1, D19.A, J73.2, J74.2, J76.2, JP55.2, JP57.1, R132.P$2, R133.P$1, U37.8, U38.8
VCC19: C20.1, D20.A, J77.2, J78.2, J80.2, JP58.2, JP60.1, R139.P$2, R140.P$1, U39.8, U40.8
VCC20: C21.1, D21.A, J81.2, J82.2, J84.2, JP61.2, JP63.1, R146.P$2, R147.P$1, U41.8, U42.8
VCC21: C22.1, D22.A, J85.2, J86.2, J88.2, JP64.2, JP66.1, R153.P$2, R154.P$1, U43.8, U44.8
VCC22: C23.1, D23.A, J89.2, J90.2, J92.2, JP67.2, JP69.1, R160.P$2, R161.P$1, U45.8, U46.8
VCC23: C24.1, D24.A, J93.2, J94.2, J96.2, JP70.2, JP72.1, R167.P$2, R168.P$1, U47.8, U48.8
VCC24: C25.1, D25.A, J97.2, J98.2, J100.2, JP73.2, JP75.1, R174.P$2, R175.P$1, U49.8, U50.8
VCC25: C26.1, D26.A, J101.2, J102.2, J104.2, JP76.2, JP78.1, R181.P$2, R182.P$1, U51.8, U52.8
VCC26: C27.1, D27.A, J105.2, J106.2, J108.2, JP79.2, JP81.1, R188.P$2, R189.P$1, U53.8, U54.8

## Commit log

2018-03-26 removed original files
2018-03-26 updated board to sfe standards
2018-03-26 PWR label
2018-03-30 post checklist changes
2018-03-30 fixed text issue
2018-05-07 post review changes
2018-05-08 updated silk for name, post QC changes
2018-05-08 cleaned repo
2018-05-08 added buzzard finger labels
2018-05-09 changed to Trace Jumper
2018-05-09 created panel v10
2018-05-11 Added panel
2018-07-17 updating repo for release
2018-07-17 Squashed 'Libraries/Arduino/' content from commit df423cb
    git-subtree-dir: Libraries/Arduino
    git-subtree-split: df423cb850072d5ad2a2f6ba829ed9c92971c209

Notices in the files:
parts and their libraries:
SparkFun-Aesthetics: Licensing: Creative Commons ShareAlike 4.0 International - https://creativecommons.org/licenses/by-sa/4.0
SparkFun-Aesthetics: Released under the Creative Commons Attribution Share-Alike 4.0 License
SparkFun-Aesthetics: https://creativecommons.org/licenses/by-sa/4.0
